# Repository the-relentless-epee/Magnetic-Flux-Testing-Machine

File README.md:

# Magnetic-Flux-Testing-Machine
A machine to collect data on how magnetic flux changes over distance. The end goal is to test how the air gap in an electric motor affects its performance. The machine involves spinning a disc of neodynium magnets next to a coil. The distance between the magnet disc and the coil is changed using a stepper motor, and the voltage across the coil is measured.

**Overall Assembly:**

**PCB:**

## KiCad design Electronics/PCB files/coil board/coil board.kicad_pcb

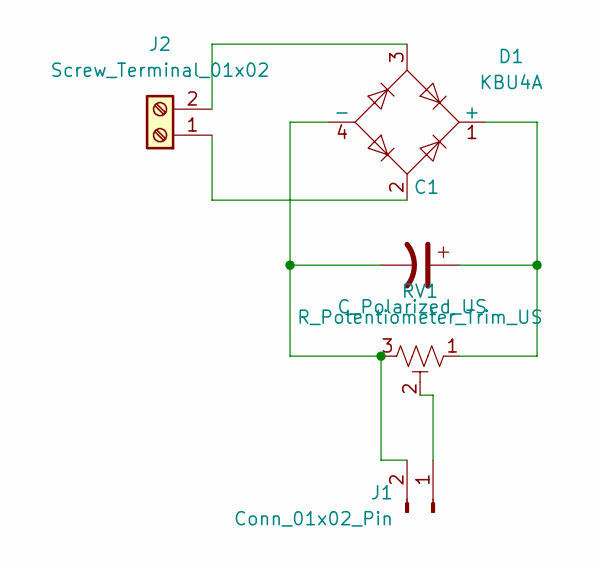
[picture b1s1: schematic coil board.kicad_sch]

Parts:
C1: C_Polarized_US; CP_Radial_D4.0mm_P2.00mm
D1: KBU4A; Diode_Bridge_Vishay_KBU
J1: Conn_01x02_Pin; PinHeader_1x02_P2.54mm_Vertical
J2: Screw_Terminal_01x02; TerminalBlock_RND_205-00232_1x02_P5.08mm_Horizontal
RV1: R_Potentiometer_Trim_US; Potentiometer_Vishay_T93YA_Vertical

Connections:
unnamed: C1.1, D1.1 (+), RV1.1
unnamed: C1.2, D1.4 (-), J1.2, RV1.3
unnamed: J1.1, RV1.2
unnamed: D1.2, J2.1
unnamed: D1.3, J2.2

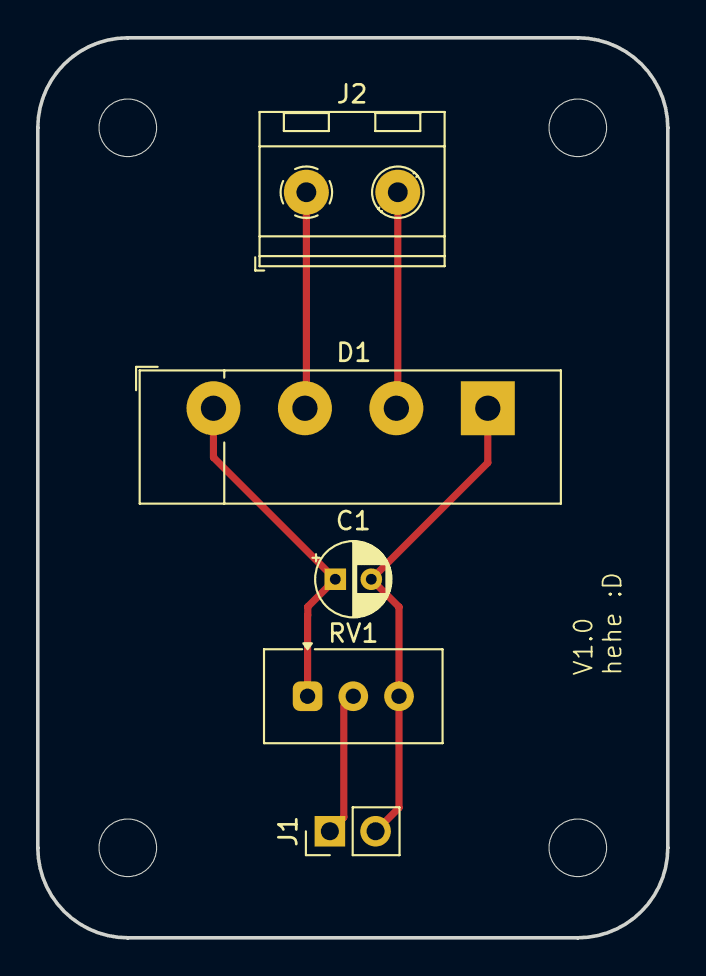
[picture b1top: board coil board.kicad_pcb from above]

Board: 2 copper layers, 35.0 x 50.0 mm, 5 parts (0 on the bottom side), 5 nets.

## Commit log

2024-08-02 550 motor mount upload
    V1 of the "spindle" motor mount. Uses 550 DC motor, mounts onto a commonly available V-roller carriage with M5 screws. included a spot to mount a microswitch for homing.
2024-08-02 added 8x magnet rotor disc for 550 DC motor
2024-08-03 added legs (mirror of each other)
    this is a "base" that screws onto the v-slot extrusion using M4 T-nuts. Made so that the center of gravity of the whole machine is well supported.
2024-08-03 added stepper mount for linear movement
    uses gt2 pulley, designed to be as close to the extrusion as possible.
2024-08-03 added coil and tool for winding the wires
    uses 0.2mm enameled copper wire. ~200 turns each, 4 in total. The two halves fit over each other and should be glued.
2024-08-03 added body to mount 4 coils to extrusion
    uses m3 bolts and t-nuts to mount to extrusion. Coils are glued to their alignment slots
2024-08-04 initial function tests for hardware
    - tests stepper homing with microswitch
    - creating data buffers for high speed adc reading
    - logging value to an SD module
2024-08-04 added circuit design for power distribution board
2024-08-04 organized files
2024-08-04 added coil board schematics
2024-08-04 added case for circuit boards
    case for power board and coil adapter board
2024-08-05 added base for circuit boards
2024-08-09 added stl files
2024-08-13 added main code
2024-08-15 added assembly images
2024-08-15 re-wrote code
    this V2 code uses standard units, all stepper movements are expressed as relationship between variables. Main function to cycle through distances is improved. Minor debugging with SD card section.
    now clears the datalog file before each testing cycle.
2024-08-15 encoder mount
2024-08-24 added PCB design
2024-08-24 power distribution board PCB design
2024-08-24 added python data analysis code
2024-09-09 Update README.md
    added images
